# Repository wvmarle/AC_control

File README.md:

# AC_control
Arduino library for AC phase controller with peak detection.

This library controls AC power through phase cutting, with a synchronisation signal based on peak detection rather than zero crossing detection. It makes use of pin change interrupts (on PORTD) and Timer1.

Please note:
SYNC_PIN (receiving the peak transition pulse) must be conneted to a pin in PORTD, i.e. one of the digital pins 2-7.
GATE_PIN can be connected to any digital or analog pin (except A6/A7).
This library uses pin change interrupt on PORTD. This will cause problems if used with another library that tries to use the same interrupt vector (PCINT2_vect).
This library uses Timer1 and timer interrupts.
This library supports only one AC control unit per Arduino.
It is currently limited to 50 Hz AC (this is a code limitation).

Phase cutting is an AC control technique using a TRIAC to control how much of the waveform is let through to the device. The later in the wave the TRIAC is switched on, the less power is transferred to the connected device.

Schematics
-

In the ./schematics folder are the complete schematics and PCB development files. 

The V1 PCB has been tested and was found to have some issues: the TRIAC was connected incorrectly, and an optocoupler footprint was wrong. These issues have been corrected in the development version in the root directory.

The schematic has been tested by reworking bits of the V1 PCB, but the redesigned PCB has not been tested as such.

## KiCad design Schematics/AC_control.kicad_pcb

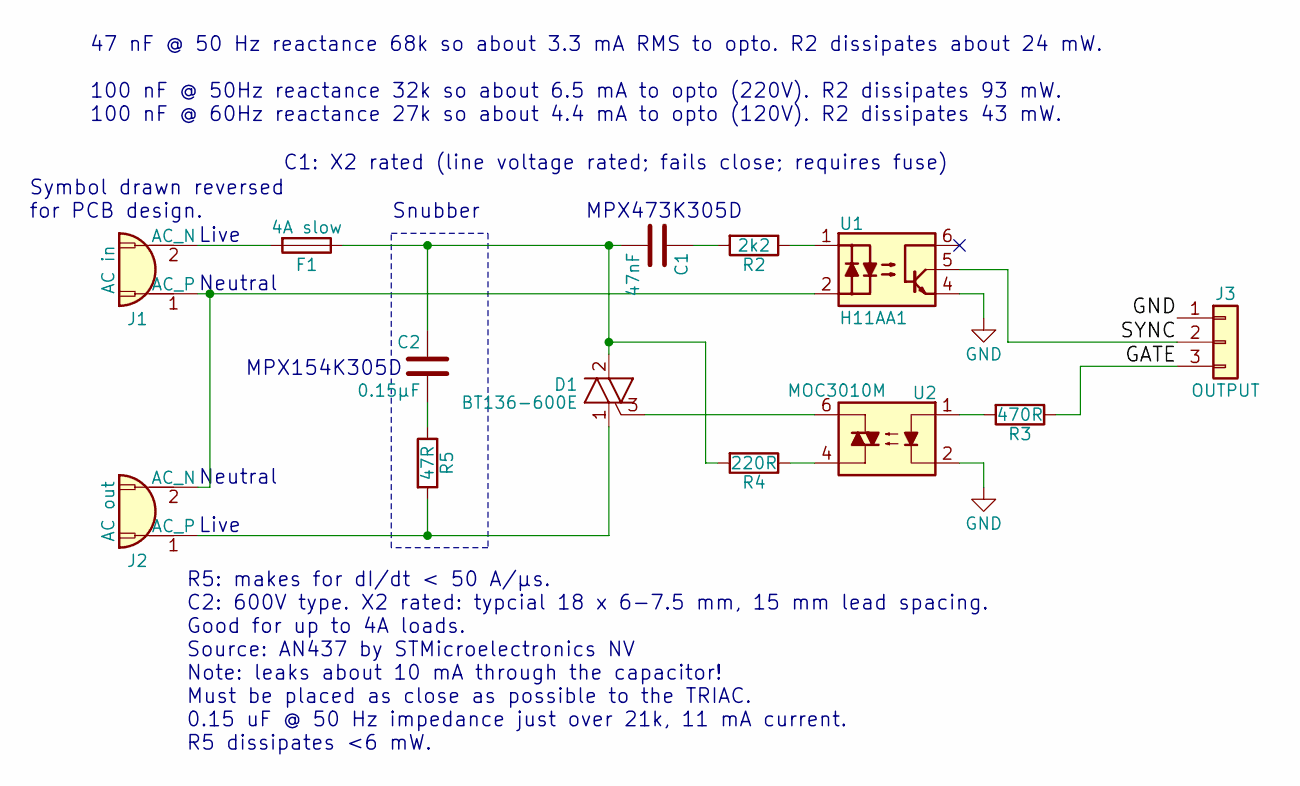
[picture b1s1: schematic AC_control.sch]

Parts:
C1: 47nF; C_Rect_L18.0mm_W5.0mm_P15.00mm_FKS3_FKP3
C2: 0.15µF; C_Rect_L18.0mm_W6.0mm_P15.00mm_FKS3_FKP3
D1: BT136-600E; TO-220-3_Vertical
F1: 4A slow; PTF-78_fuseholder
J1: AC in; TerminalBlock_KF129_P5.08mm
J2: AC out; TerminalBlock_KF129_P5.08mm
J3: OUTPUT; JST_XH_B03B-XH-A_03x2.50mm_Straight
R2: 2k2; R_Axial_DIN0207_L6.3mm_D2.5mm_P7.62mm_Horizontal
R3: 470R; R_Axial_DIN0207_L6.3mm_D2.5mm_P7.62mm_Horizontal
R4: 220R; R_Axial_DIN0207_L6.3mm_D2.5mm_P7.62mm_Horizontal
R5: 47R; R_Axial_DIN0207_L6.3mm_D2.5mm_P7.62mm_Horizontal
U1: H11AA1; DIP-6_W7.62mm
U2: MOC3010M; DIP-6_W7.62mm

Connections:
/GATE: J3.3, R3.1
/SYNC: J3.2, U1.5
GND: J3.1, U1.4, U2.2
unnamed: C1.1, R2.2
unnamed: C1.2, C2.1, D1.2 (MT2), F1.1, R4.2
unnamed: C2.2, R5.1
unnamed: D1.1 (MT1), J2.1 (AC_P), R5.2
unnamed: D1.3 (G), U2.6
unnamed: F1.2, J1.2 (AC_N)
unnamed: J1.1 (AC_P), J2.2 (AC_N), U1.2
unnamed: R2.1, U1.1
unnamed: R3.2, U2.1
unnamed: R4.1, U2.4

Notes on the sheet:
C1: X2 rated (line voltage rated; fails close; requires fuse)
Snubber
R5: makes for dI/dt < 50 A/µs. C2: 600V type. X2 rated: typcial 18 x 6-7.5 mm, 15 mm lead spacing. Good for up to 4A loads. Source: AN437 by STMicroelectronics NV Note: leaks about 10 mA through the capacitor! Must be placed as close as possible to the TRIAC. 0.15 uF @ 50 Hz impedance just over 21k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
MPX154K305D
MPX473K305D
47 nF @ 50 Hz reactance 68k so about 3.3 mA RMS to opto. R2 dissipates about 24 mW. 100 nF @ 50Hz reactance 32k so about 6.5 mA to opto (220V). R2 dissipates 93 mW. 100 nF @ 60Hz reactance 27k so about 4.4 mA to opto (120V). R2 dissipates 43 mW.
Live
Neutral
Symbol drawn reversed for PCB design.

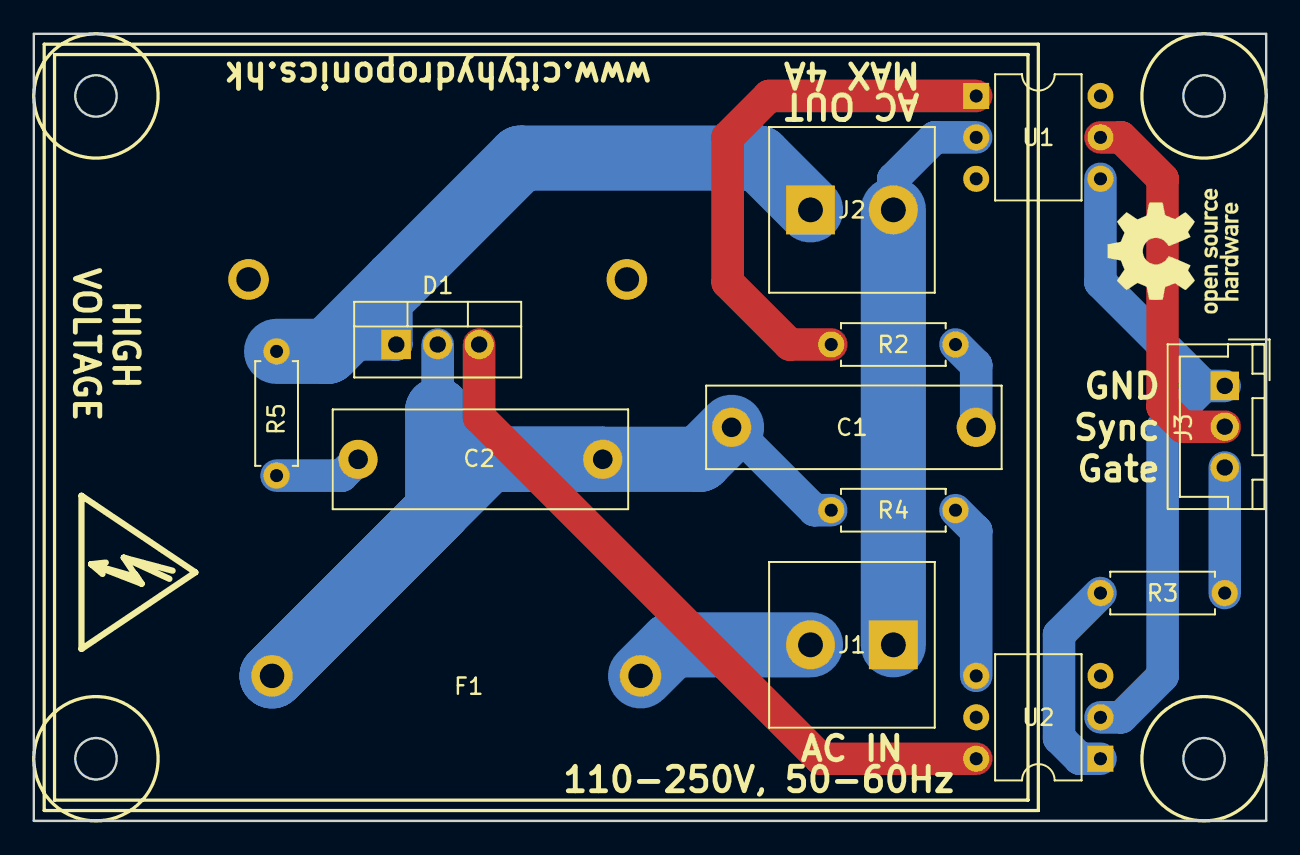
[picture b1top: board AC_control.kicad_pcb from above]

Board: 2 copper layers, 75.6 x 48.3 mm, 13 parts (0 on the bottom side), 13 nets.

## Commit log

2018-07-16 Updated comments, improved state management.
2018-07-16 Added schematic diagram image.
2018-07-29 Bugfixes
2018-10-17 Updated schematic
2018-10-17 V1 schematic
    Used for prototypes.
2018-10-29 Added support for 60Hz mains.
2021-08-03 Added schematics & PCB files.
